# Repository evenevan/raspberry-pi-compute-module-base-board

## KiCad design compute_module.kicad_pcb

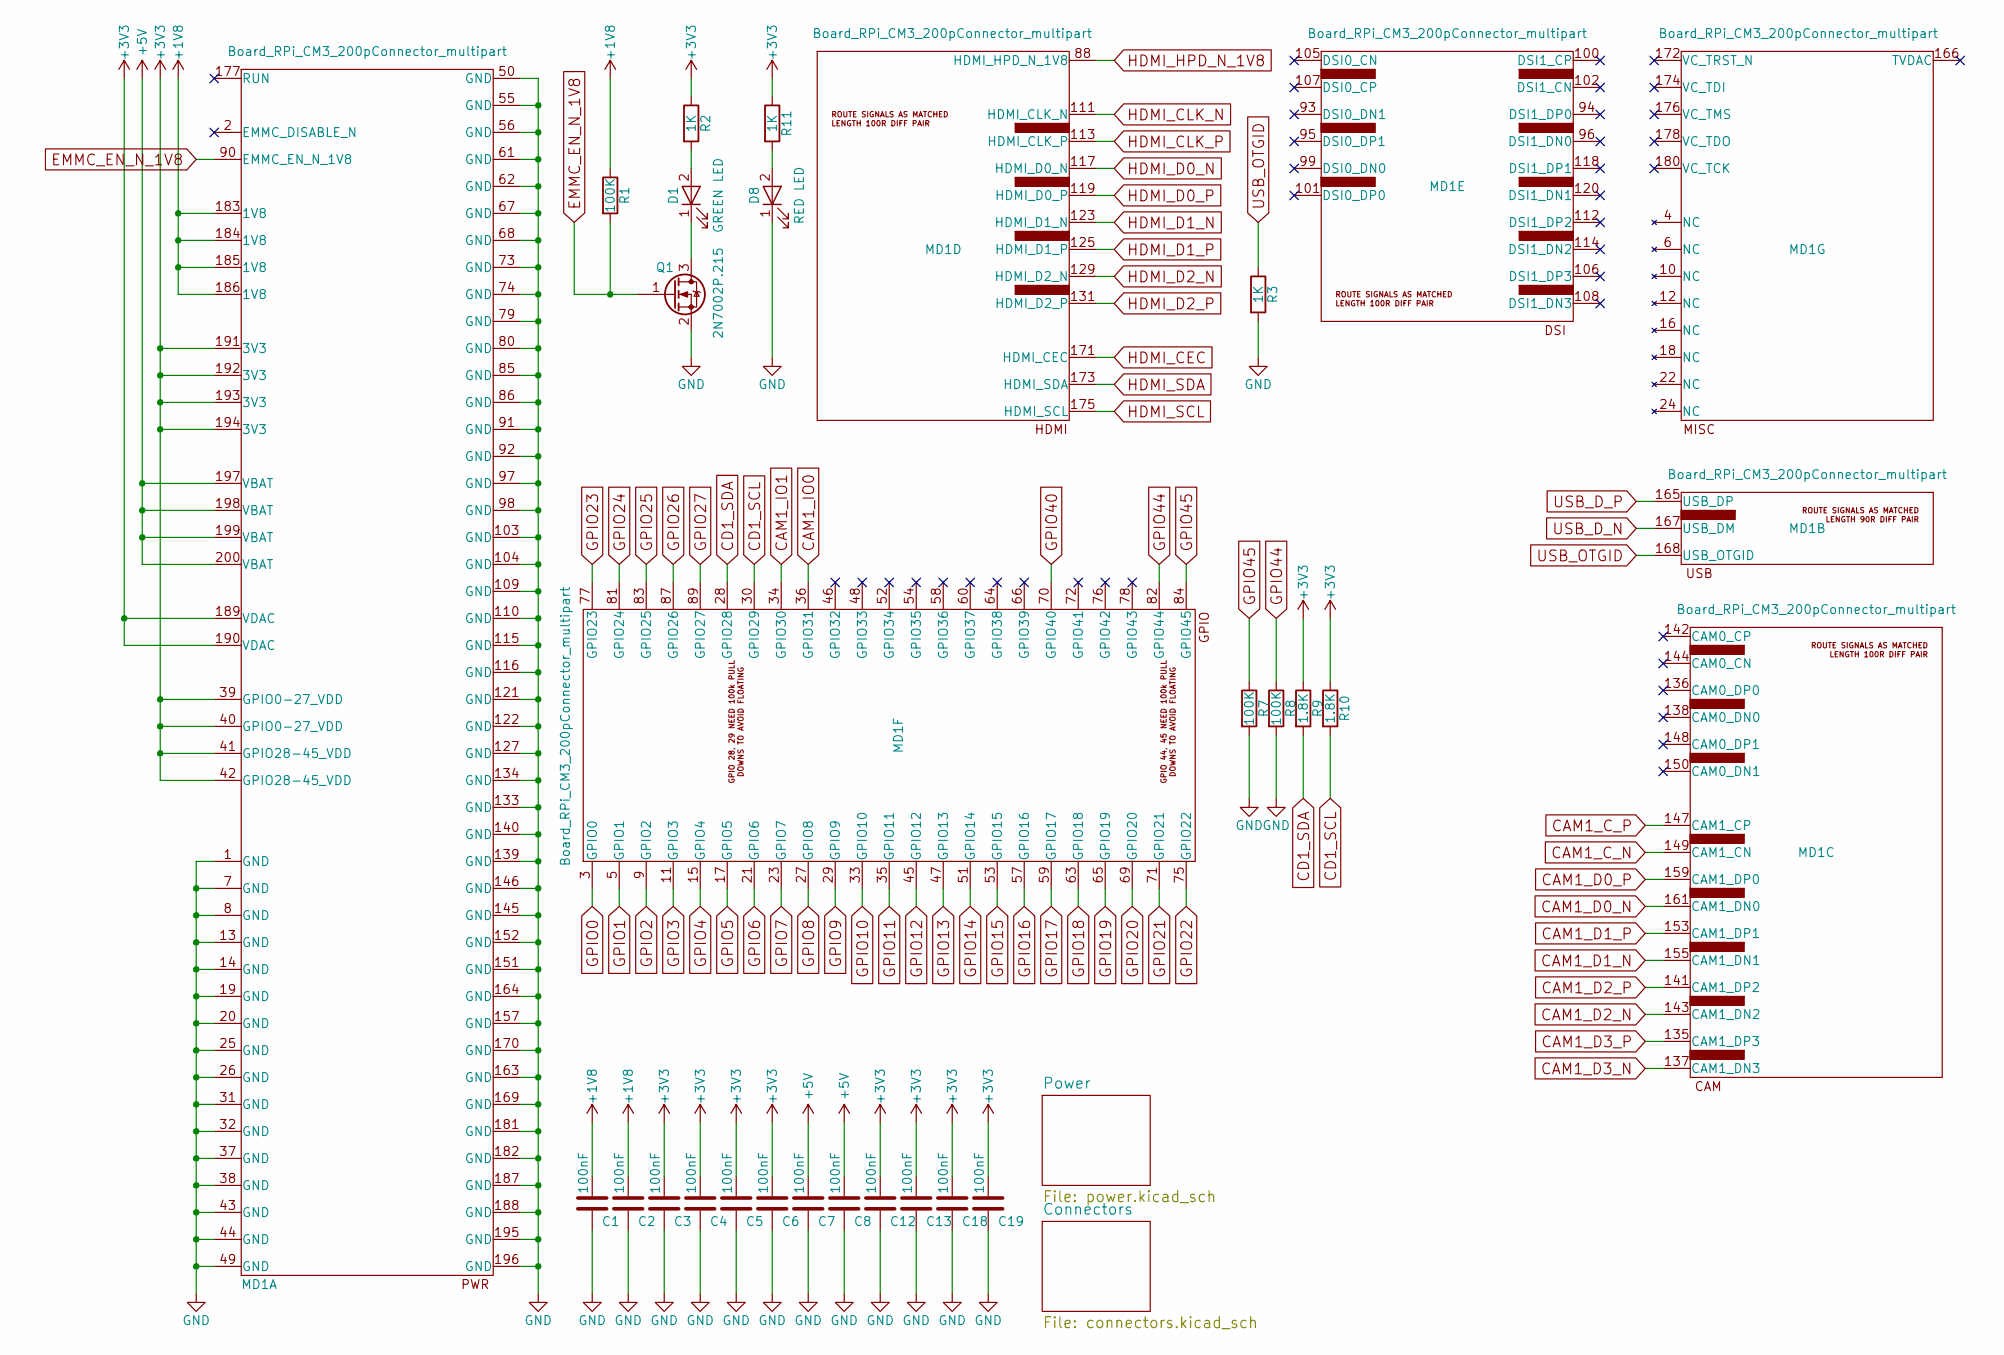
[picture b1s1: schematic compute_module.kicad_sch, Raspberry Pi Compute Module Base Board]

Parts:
C1, C2, C3, C4, C5, C6, C7, C8, C12, C13, C18, C19: 100nF; C_0402
D1: GREEN LED; LED_0805
D8: RED LED; LED_0805
MD1: Board_RPi_CM3_200pConnector_multipart; Conn_TE-DDR2-SODIMM-0.6-200P-doublesided
Q1: 2N7002P.215; SOT-23
R1, R7, R8: 100K; R_0603_HandSoldering
R2, R3, R11: 1K; R_0603_HandSoldering
R9, R10: 1.8K; R_0603_HandSoldering

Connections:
+1V8: C1.1, C2.1, MD1.183 (1V8), MD1.184 (1V8), MD1.185 (1V8), MD1.186 (1V8), R1.1; also elsewhere on the board
+3V3: C3.1, C4.1, C5.1, C6.1, C12.1, C13.1, C18.1, C19.1, MD1.39 (GPIO0-27_VDD), MD1.40 (GPIO0-27_VDD), MD1.41 (GPIO28-45_VDD), MD1.42 (GPIO28-45_VDD), MD1.189 (VDAC), MD1.190 (VDAC), MD1.191 (3V3), MD1.192 (3V3), MD1.193 (3V3), MD1.194 (3V3), R2.1, R9.1, R10.1, R11.1; also elsewhere on the board
+5V: C7.1, C8.1, MD1.197 (VBAT), MD1.198 (VBAT), MD1.199 (VBAT), MD1.200 (VBAT); also elsewhere on the board
CAM1_C_N: MD1.149 (CAM1_CN); also elsewhere on the board
CAM1_C_P: MD1.147 (CAM1_CP); also elsewhere on the board
CAM1_D0_N: MD1.161 (CAM1_DN0); also elsewhere on the board
CAM1_D0_P: MD1.159 (CAM1_DP0); also elsewhere on the board
CAM1_D1_N: MD1.155 (CAM1_DN1); also elsewhere on the board
CAM1_D1_P: MD1.153 (CAM1_DP1); also elsewhere on the board
CAM1_D2_N: MD1.143 (CAM1_DN2); also elsewhere on the board
CAM1_D2_P: MD1.141 (CAM1_DP2); also elsewhere on the board
CAM1_D3_N: MD1.137 (CAM1_DN3); also elsewhere on the board
CAM1_D3_P: MD1.135 (CAM1_DP3); also elsewhere on the board
CAM1_IO0: MD1.36 (GPIO31); also elsewhere on the board
CAM1_IO1: MD1.34 (GPIO30); also elsewhere on the board
CD1_SCL: MD1.30 (GPIO29), R10.2; also elsewhere on the board
CD1_SDA: MD1.28 (GPIO28), R9.2; also elsewhere on the board
EMMC_EN_N_1V8: MD1.90 (EMMC_EN_N_1V8), Q1.1 (G), R1.2
GND: C1.2, C2.2, C3.2, C4.2, C5.2, C6.2, C7.2, C8.2, C12.2, C13.2, C18.2, C19.2, D8.1 (K), MD1.1 (GND), MD1.7 (GND), MD1.8 (GND), MD1.13 (GND), MD1.14 (GND), MD1.19 (GND), MD1.20 (GND), MD1.25 (GND), MD1.26 (GND), MD1.31 (GND), MD1.32 (GND), MD1.37 (GND), MD1.38 (GND), MD1.43 (GND), MD1.44 (GND), MD1.49 (GND), MD1.50 (GND), MD1.55 (GND), MD1.56 (GND), MD1.61 (GND), MD1.62 (GND), MD1.67 (GND), MD1.68 (GND), MD1.73 (GND), MD1.74 (GND), MD1.79 (GND), MD1.80 (GND), MD1.85 (GND), MD1.86 (GND), MD1.91 (GND), MD1.92 (GND), MD1.97 (GND), MD1.98 (GND), MD1.103 (GND), MD1.104 (GND), MD1.109 (GND), MD1.110 (GND), MD1.115 (GND), MD1.116 (GND), MD1.121 (GND), MD1.122 (GND), MD1.127 (GND), MD1.133 (GND), MD1.134 (GND), MD1.139 (GND), MD1.140 (GND), MD1.145 (GND), MD1.146 (GND), MD1.151 (GND), MD1.152 (GND), MD1.157 (GND), MD1.163 (GND), MD1.164 (GND), MD1.169 (GND), MD1.170 (GND), MD1.181 (GND), MD1.182 (GND), MD1.187 (GND), MD1.188 (GND), MD1.195 (GND), MD1.196 (GND), Q1.2 (S), R3.2, R7.2, R8.2; also elsewhere on the board
GPIO0: MD1.3 (GPIO0); also elsewhere on the board
GPIO1: MD1.5 (GPIO1); also elsewhere on the board
GPIO2: MD1.9 (GPIO2); also elsewhere on the board
GPIO3: MD1.11 (GPIO3); also elsewhere on the board
GPIO4: MD1.15 (GPIO4); also elsewhere on the board
GPIO5: MD1.17 (GPIO5); also elsewhere on the board
GPIO6: MD1.21 (GPIO6); also elsewhere on the board
GPIO7: MD1.23 (GPIO7); also elsewhere on the board
GPIO8: MD1.27 (GPIO8); also elsewhere on the board
GPIO9: MD1.29 (GPIO9); also elsewhere on the board
GPIO10: MD1.33 (GPIO10); also elsewhere on the board
GPIO11: MD1.35 (GPIO11); also elsewhere on the board
GPIO12: MD1.45 (GPIO12); also elsewhere on the board
GPIO13: MD1.47 (GPIO13); also elsewhere on the board
GPIO14: MD1.51 (GPIO14); also elsewhere on the board
GPIO15: MD1.53 (GPIO15); also elsewhere on the board
GPIO16: MD1.57 (GPIO16); also elsewhere on the board
GPIO17: MD1.59 (GPIO17); also elsewhere on the board
GPIO18: MD1.63 (GPIO18); also elsewhere on the board
GPIO19: MD1.65 (GPIO19); also elsewhere on the board
GPIO20: MD1.69 (GPIO20); also elsewhere on the board
GPIO21: MD1.71 (GPIO21); also elsewhere on the board
GPIO22: MD1.75 (GPIO22); also elsewhere on the board
GPIO23: MD1.77 (GPIO23); also elsewhere on the board
GPIO24: MD1.81 (GPIO24); also elsewhere on the board
GPIO25: MD1.83 (GPIO25); also elsewhere on the board
GPIO26: MD1.87 (GPIO26); also elsewhere on the board
GPIO27: MD1.89 (GPIO27); also elsewhere on the board
GPIO40: MD1.70 (GPIO40); also elsewhere on the board
GPIO44: MD1.82 (GPIO44), R8.1
GPIO45: MD1.84 (GPIO45), R7.1; also elsewhere on the board
HDMI_CEC: MD1.171 (HDMI_CEC); also elsewhere on the board
HDMI_CLK_N: MD1.111 (HDMI_CLK_N); also elsewhere on the board
HDMI_CLK_P: MD1.113 (HDMI_CLK_P); also elsewhere on the board
HDMI_D0_N: MD1.117 (HDMI_D0_N); also elsewhere on the board
HDMI_D0_P: MD1.119 (HDMI_D0_P); also elsewhere on the board
HDMI_D1_N: MD1.123 (HDMI_D1_N); also elsewhere on the board
HDMI_D1_P: MD1.125 (HDMI_D1_P); also elsewhere on the board
HDMI_D2_N: MD1.129 (HDMI_D2_N); also elsewhere on the board
HDMI_D2_P: MD1.131 (HDMI_D2_P); also elsewhere on the board
HDMI_HPD_N_1V8: MD1.88 (HDMI_HPD_N_1V8); also elsewhere on the board
HDMI_SCL: MD1.175 (HDMI_SCL); also elsewhere on the board
HDMI_SDA: MD1.173 (HDMI_SDA); also elsewhere on the board
unnamed: D1.2 (A), R2.2
unnamed: D1.1 (K), Q1.3 (D)
unnamed: D8.2 (A), R11.2
USB_D_N: MD1.167 (USB_DM); also elsewhere on the board
USB_D_P: MD1.165 (USB_DP); also elsewhere on the board
USB_OTGID: MD1.168 (USB_OTGID), R3.1

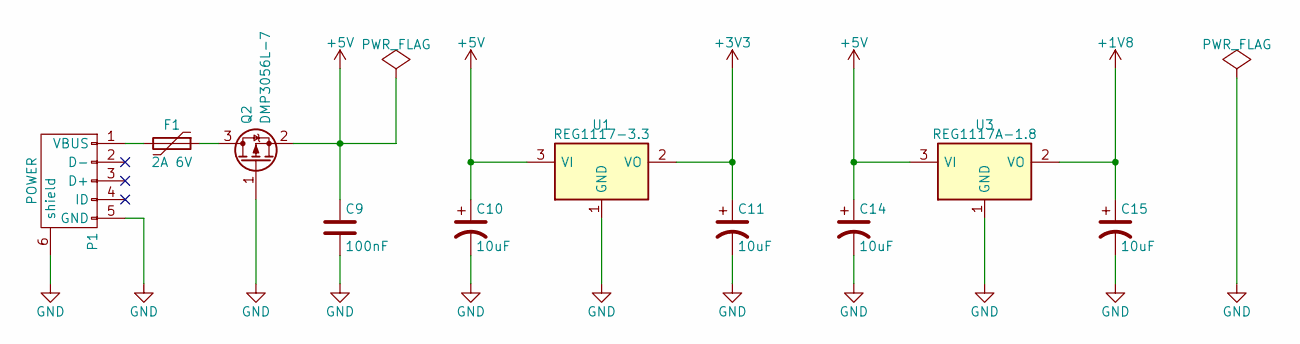
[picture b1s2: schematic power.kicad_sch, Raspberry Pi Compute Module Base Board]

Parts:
C9: 100nF; C_0402
C10, C11, C14, C15: 10uF; CP_Tantalum_Case-C_EIA-6032-28_Reflow
F1: 2A 6V; Polyfuse_0805
P1: POWER; USB_Micro-B
Q2: DMP3056L-7; SOT-23
U1: REG1117-3.3; SOT-223-3_TabPin2
U3: REG1117A-1.8; SOT-223-3_TabPin2

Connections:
+1V8: C15.1, U3.2 (VO); also elsewhere on the board
+3V3: C11.1, U1.2 (VO); also elsewhere on the board
+5V: C9.1, C10.1, C14.1, Q2.2 (S), U1.3 (VI), U3.3 (VI); also elsewhere on the board
GND: C9.2, C10.2, C11.2, C14.2, C15.2, P1.5 (GND), P1.6 (shield), Q2.1 (G), U1.1 (GND), U3.1 (GND); also elsewhere on the board
unnamed: F1.2, P1.1 (VBUS)
unnamed: F1.1, Q2.3 (D)

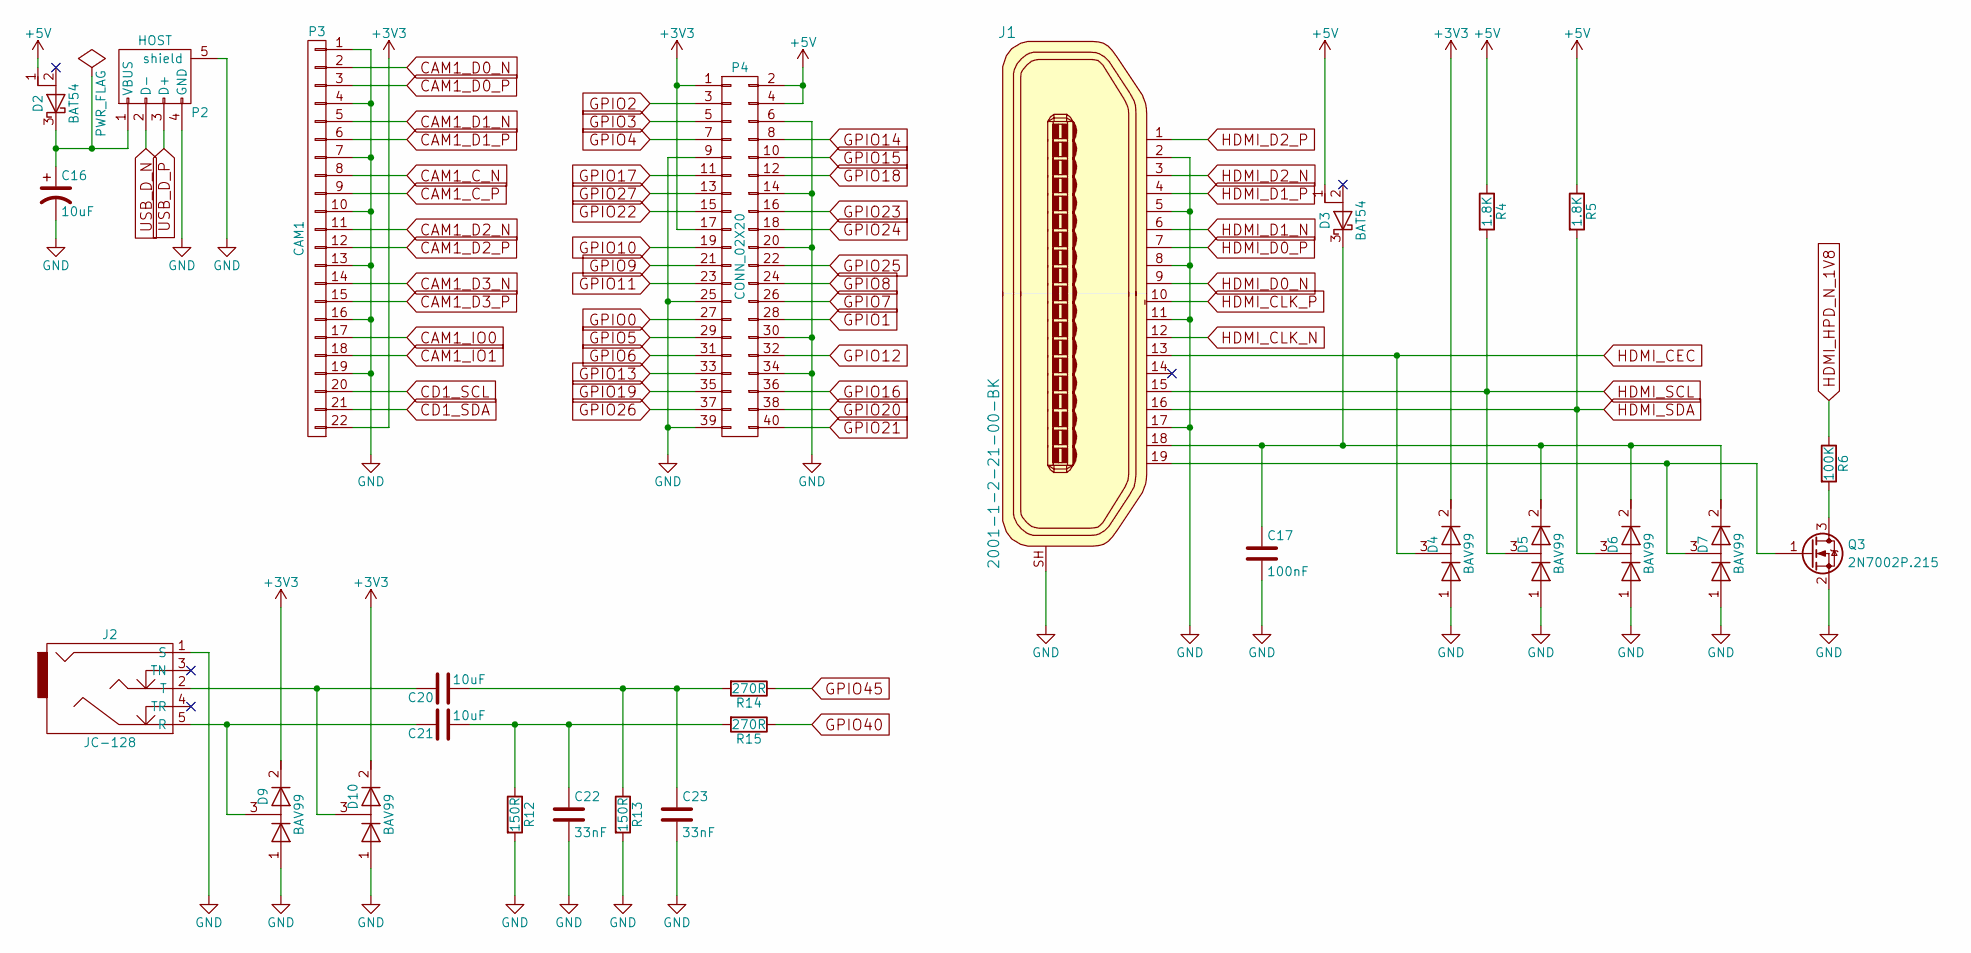
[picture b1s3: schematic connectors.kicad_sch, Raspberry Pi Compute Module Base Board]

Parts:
C16: 10uF; CP_Tantalum_Case-C_EIA-6032-28_Reflow
C17: 100nF; C_0402
C20, C21: 10uF; C_0805
C22, C23: 33nF; C_0402
D2, D3: BAT54; SOT-23
D4, D5, D6, D7, D9, D10: BAV99; SOT-23
J1: 2001-1-2-21-00-BK; HDMI_MOLEX_471510001
J2: JC-128
P2: HOST; USB_A
P3: CAM1; FPC_22
P4: CONN_02X20; Pin_Header_Straight_2x20
Q3: 2N7002P.215; SOT-23
R4, R5: 1.8K; R_0603_HandSoldering
R6: 100K; R_0603_HandSoldering
R12, R13: 150R; R_0603_HandSoldering
R14, R15: 270R; R_0603_HandSoldering

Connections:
+3V3: D4.2 (K), D9.2 (K), D10.2 (K), P3.22, P4.1, P4.17; also elsewhere on the board
+5V: D2.1 (A), D3.1 (A), P4.2, P4.4, R4.1, R5.1; also elsewhere on the board
CAM1_C_N: P3.8; also elsewhere on the board
CAM1_C_P: P3.9; also elsewhere on the board
CAM1_D0_N: P3.2; also elsewhere on the board
CAM1_D0_P: P3.3; also elsewhere on the board
CAM1_D1_N: P3.5; also elsewhere on the board
CAM1_D1_P: P3.6; also elsewhere on the board
CAM1_D2_N: P3.11; also elsewhere on the board
CAM1_D2_P: P3.12; also elsewhere on the board
CAM1_D3_N: P3.14; also elsewhere on the board
CAM1_D3_P: P3.15; also elsewhere on the board
CAM1_IO0: P3.17; also elsewhere on the board
CAM1_IO1: P3.18; also elsewhere on the board
CD1_SCL: P3.20; also elsewhere on the board
CD1_SDA: P3.21; also elsewhere on the board
GND: C16.2, C17.2, C22.2, C23.2, D4.1 (A), D5.1 (A), D6.1 (A), D7.1 (A), D9.1 (A), D10.1 (A), J1.2, J1.5, J1.8, J1.11, J1.17, J1.SH, J2.1 (S), P2.4 (GND), P2.5 (shield), P3.1, P3.4, P3.7, P3.10, P3.13, P3.16, P3.19, P4.6, P4.9, P4.14, P4.20, P4.25, P4.30, P4.34, P4.39, Q3.2 (S), R12.2, R13.2; also elsewhere on the board
GPIO0: P4.27; also elsewhere on the board
GPIO1: P4.28; also elsewhere on the board
GPIO2: P4.3; also elsewhere on the board
GPIO3: P4.5; also elsewhere on the board
GPIO4: P4.7; also elsewhere on the board
GPIO5: P4.29; also elsewhere on the board
GPIO6: P4.31; also elsewhere on the board
GPIO7: P4.26; also elsewhere on the board
GPIO8: P4.24; also elsewhere on the board
GPIO9: P4.21; also elsewhere on the board
GPIO10: P4.19; also elsewhere on the board
GPIO11: P4.23; also elsewhere on the board
GPIO12: P4.32; also elsewhere on the board
GPIO13: P4.33; also elsewhere on the board
GPIO14: P4.8; also elsewhere on the board
GPIO15: P4.10; also elsewhere on the board
GPIO16: P4.36; also elsewhere on the board
GPIO17: P4.11; also elsewhere on the board
GPIO18: P4.12; also elsewhere on the board
GPIO19: P4.35; also elsewhere on the board
GPIO20: P4.38; also elsewhere on the board
GPIO21: P4.40; also elsewhere on the board
GPIO22: P4.15; also elsewhere on the board
GPIO23: P4.16; also elsewhere on the board
GPIO24: P4.18; also elsewhere on the board
GPIO25: P4.22; also elsewhere on the board
GPIO26: P4.37; also elsewhere on the board
GPIO27: P4.13; also elsewhere on the board
GPIO40: R15.1; also elsewhere on the board
GPIO45: R14.1; also elsewhere on the board
HDMI_CEC: D4.3 (common), J1.13; also elsewhere on the board
HDMI_CLK_N: J1.12; also elsewhere on the board
HDMI_CLK_P: J1.10; also elsewhere on the board
HDMI_D0_N: J1.9; also elsewhere on the board
HDMI_D0_P: J1.7; also elsewhere on the board
HDMI_D1_N: J1.6; also elsewhere on the board
HDMI_D1_P: J1.4; also elsewhere on the board
HDMI_D2_N: J1.3; also elsewhere on the board
HDMI_D2_P: J1.1; also elsewhere on the board
HDMI_HPD_N_1V8: R6.1; also elsewhere on the board
HDMI_SCL: D5.3 (common), J1.15, R4.2; also elsewhere on the board
HDMI_SDA: D6.3 (common), J1.16, R5.2; also elsewhere on the board
unnamed: C20.1, C23.1, R13.1, R14.2
unnamed: C21.1, C22.1, R12.1, R15.2
unnamed: C16.1, D2.3 (K), P2.1 (VBUS)
unnamed: C17.1, D3.3 (K), D5.2 (K), D6.2 (K), D7.2 (K), J1.18
unnamed: D7.3 (common), J1.19, Q3.1 (G)
unnamed: C21.2, D9.3 (common), J2.5 (R)
unnamed: C20.2, D10.3 (common), J2.2 (T)
unnamed: Q3.3 (D), R6.2
USB_D_N: P2.2 (D-); also elsewhere on the board
USB_D_P: P2.3 (D+); also elsewhere on the board

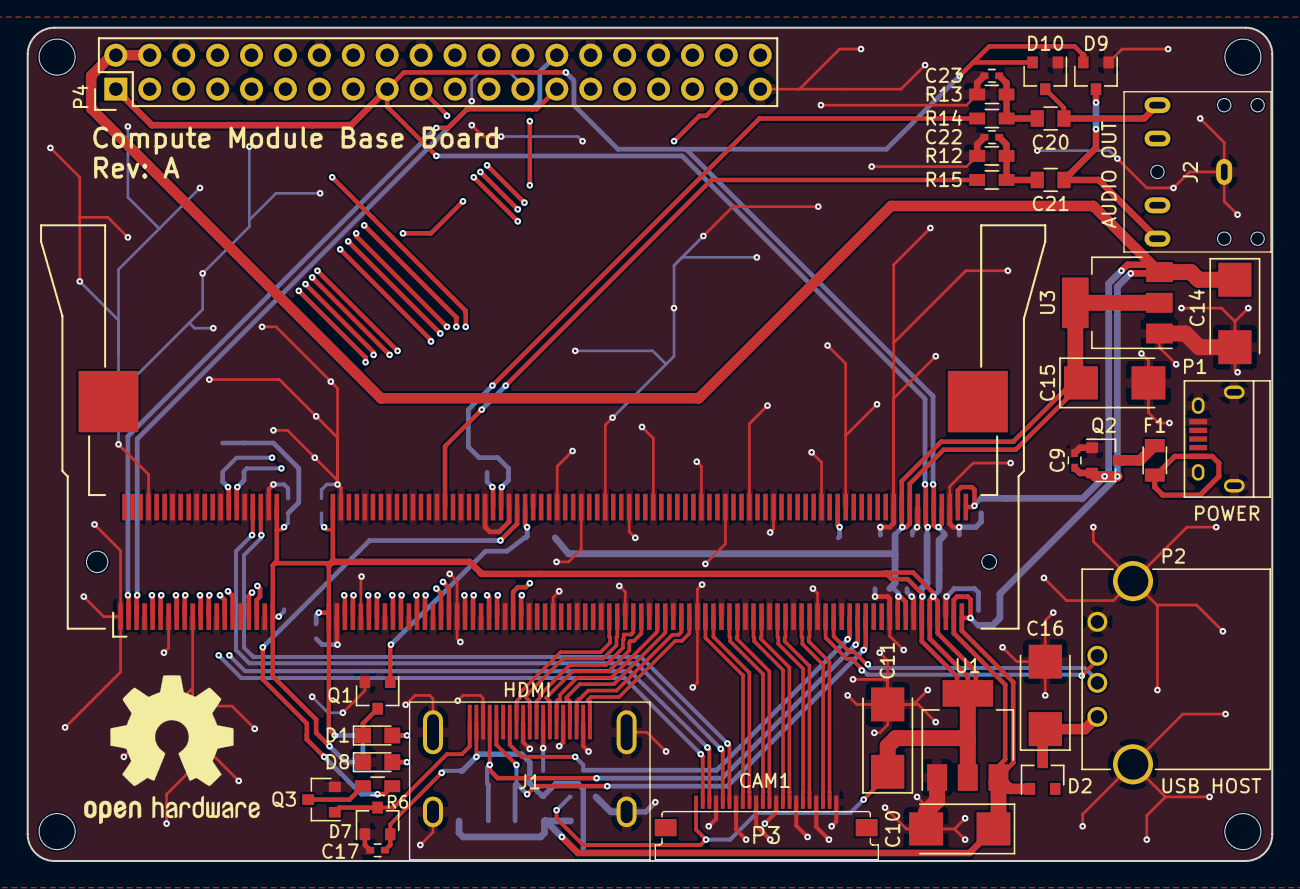
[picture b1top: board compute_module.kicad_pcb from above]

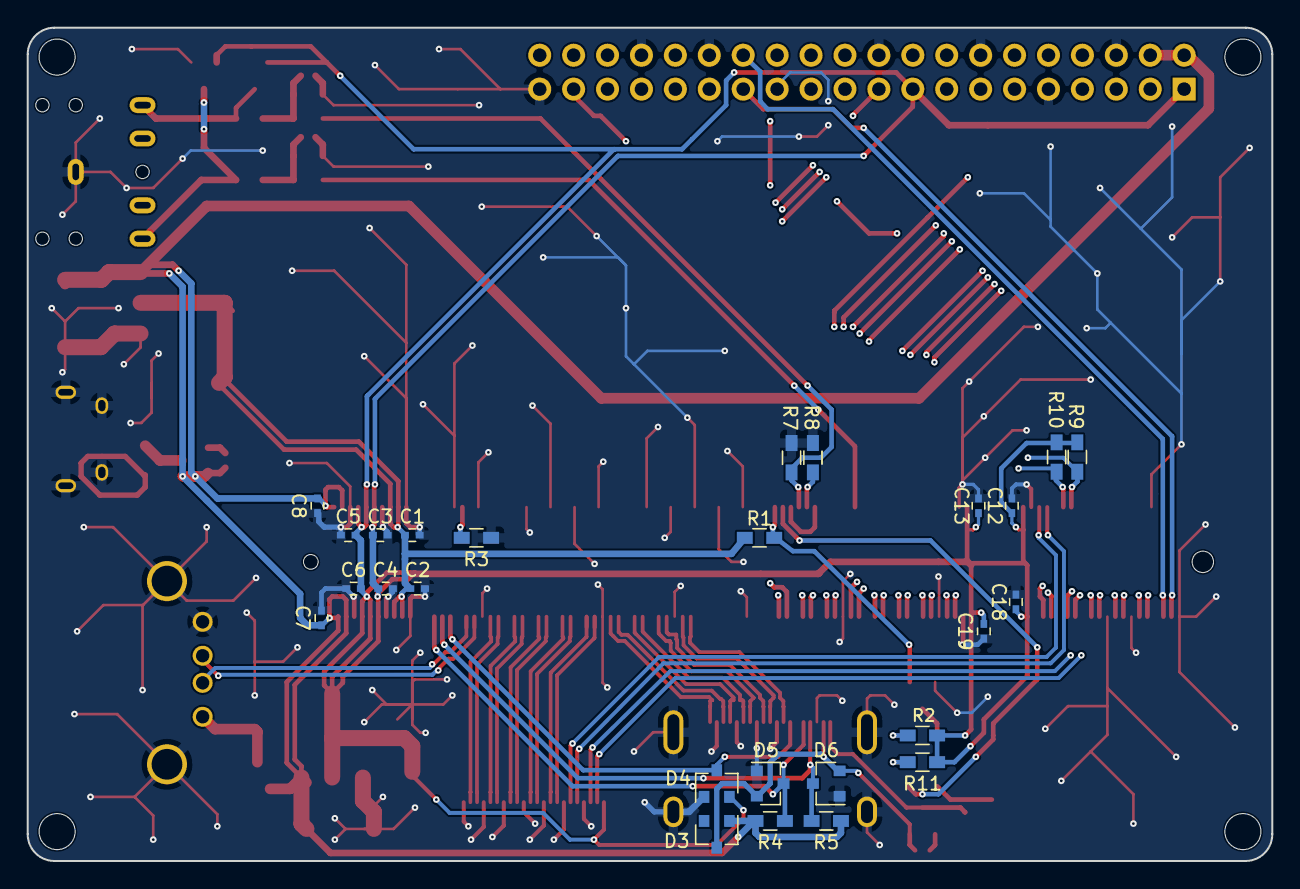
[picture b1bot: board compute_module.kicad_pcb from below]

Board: 4 copper layers, 93.2 x 62.4 mm, 61 parts (26 on the bottom side), 78 nets.

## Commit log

2026-06-06 upgrade schematic format
2026-06-06 migrate pcb
2026-06-06 migrate symbols, update footprints
2026-06-06 fix 5v erc connection
2026-06-06 fix missing hdmi junctions, dangling trace
2026-06-06 resolve remaining non footprint drc issues

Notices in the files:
compute_module.kicad_sch:
Copyright (C) 2018  Manolis Agkopian
https://www.gnu.org/licenses/gpl.html
License: GPLv3
